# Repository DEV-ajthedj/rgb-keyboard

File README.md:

My first hack club project!

This repository holds my first hack club project, which is building a keyboard complete with an ergonomic design and a cool display.

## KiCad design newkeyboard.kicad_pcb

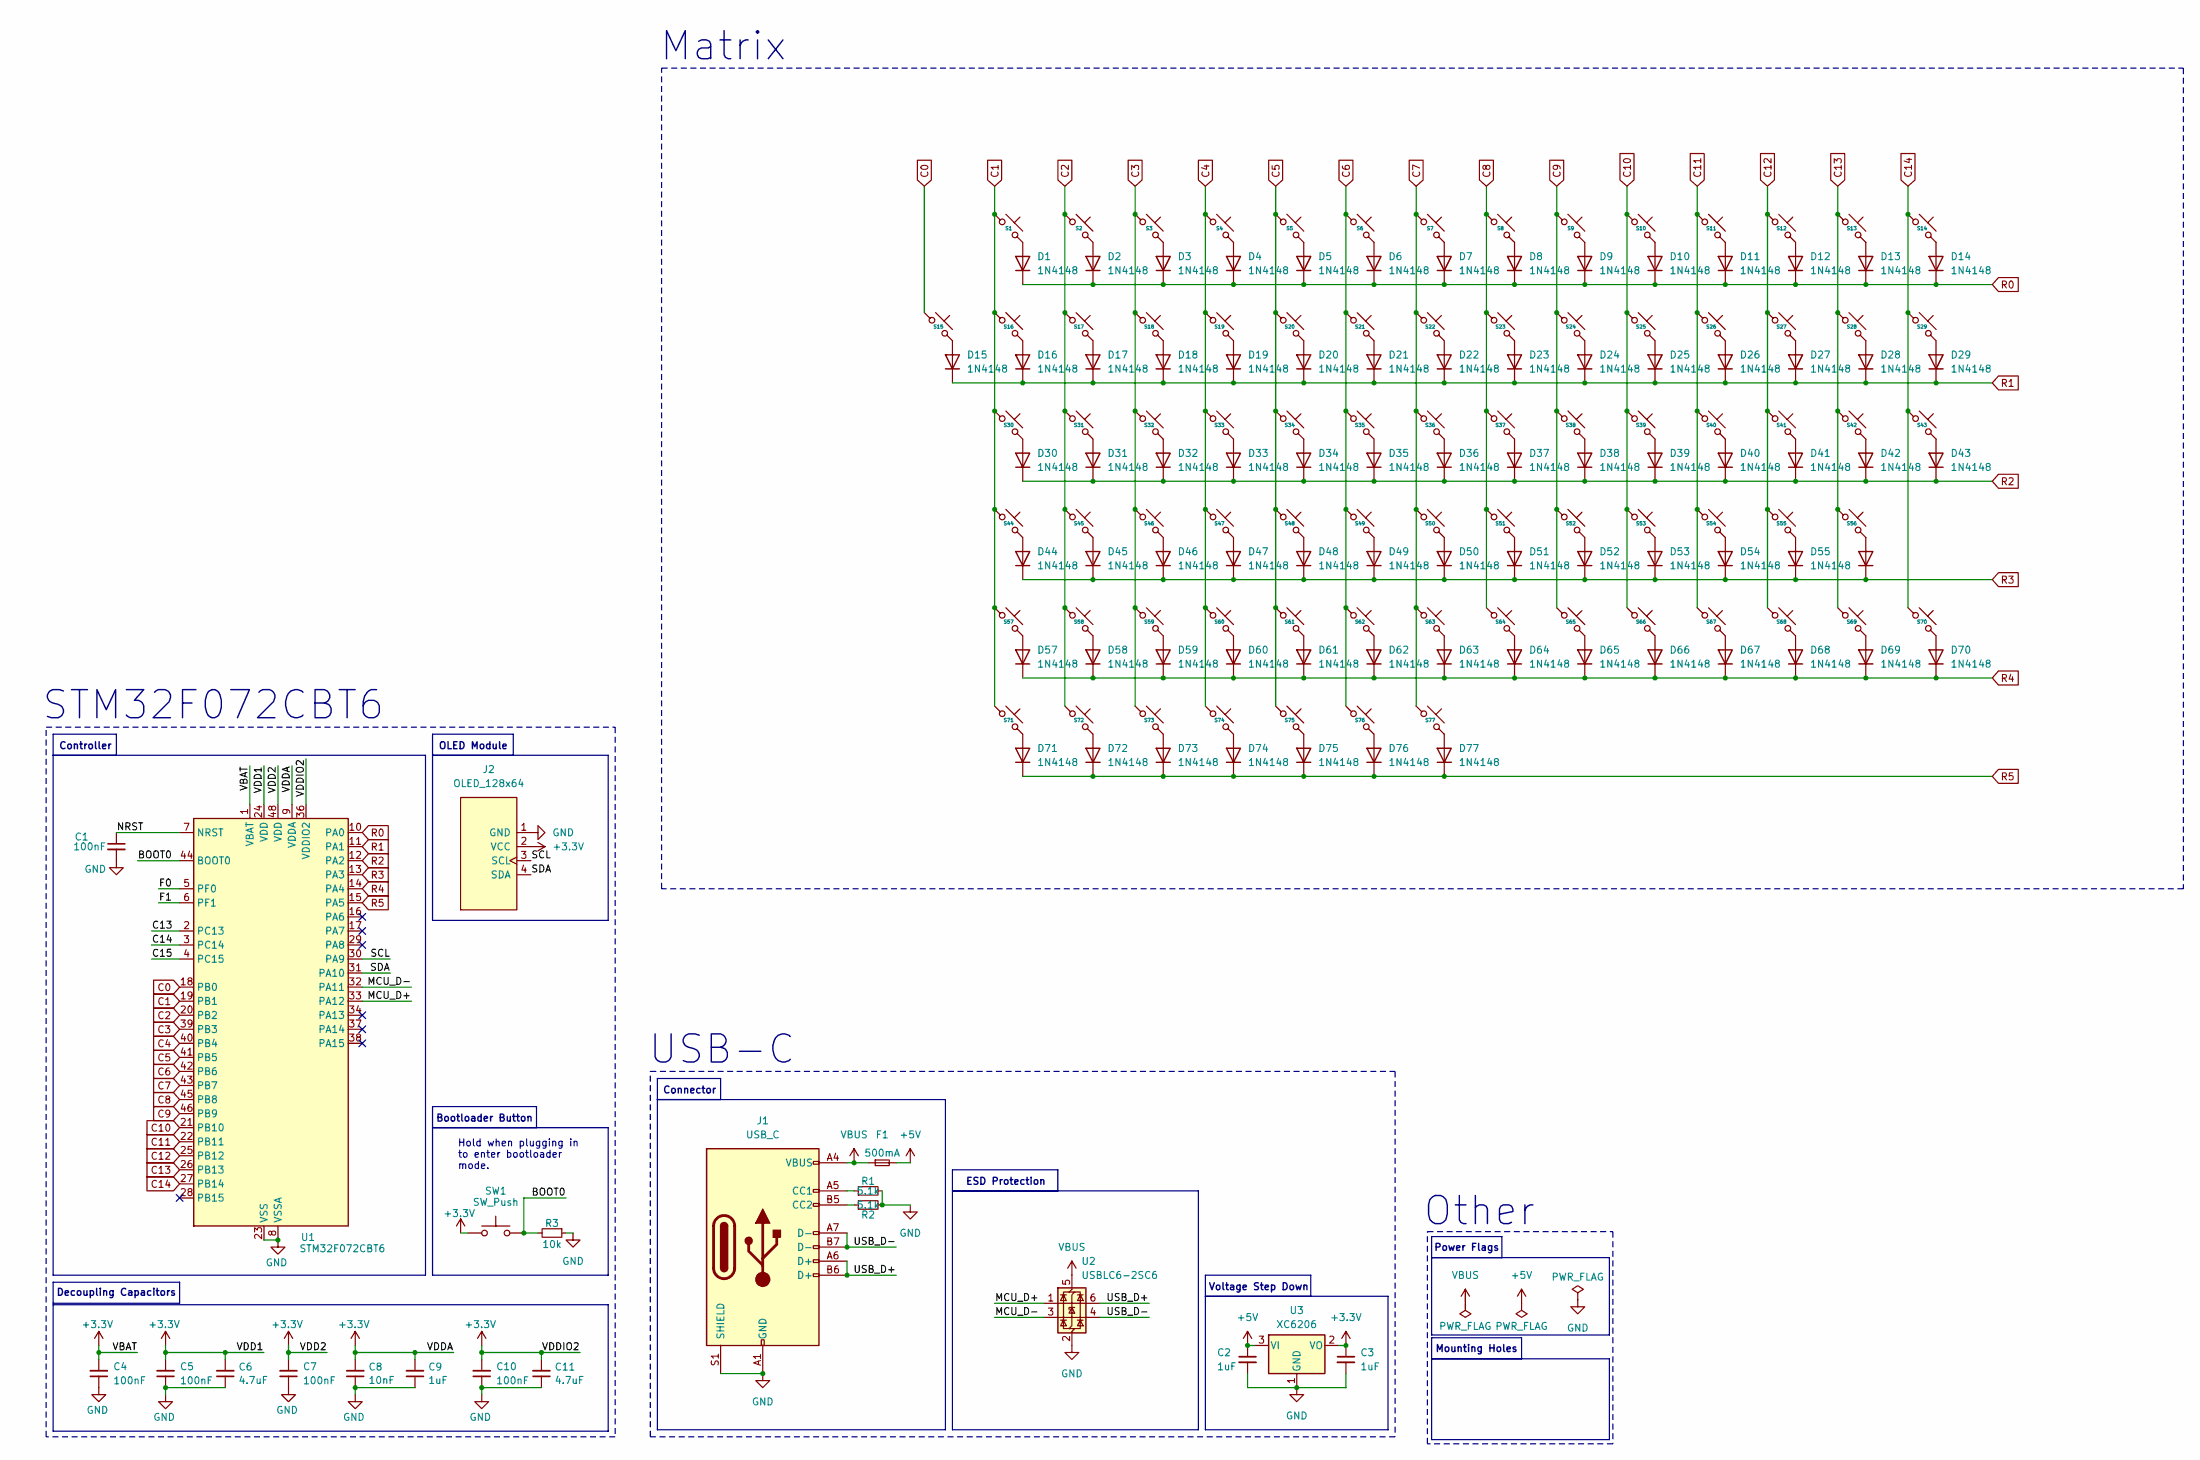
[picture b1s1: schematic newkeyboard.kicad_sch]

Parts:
C1: 100nF; Capacitor_0402; LCSC C307331
C2, C3: 1uF; Capacitor_0402; LCSC C52923
C4, C5, C7, C10: 100nF; Capacitor_0402; MPN CL05B104KB54PNC; LCSC C307331
C6, C11: 4.7uF; Capacitor_0402; MPN CL05A475MP5NRNC; LCSC C23733
C8: 10nF; Capacitor_0402; MPN CL05B103KB5NNNC; LCSC C15195
C9: 1uF; Capacitor_0402; MPN CL05A105KA5NQNC; LCSC C52923
D1, D2, D3, D4, D5, D6, D7, D8, D9, D10, D11, D12, D13, D14, D15, D16, D17, D18, D19, D20, D21, D22, D23, D24, D25, D26, D27, D28, D29, D30, D31, D32, D33, D34, D35, D36, D37, D38, D39, D40, D41, D42, D43, D44, D45, D46, D47, D48, D49, D50, D51, D52, D53, D54, D55, D56, D57, D58, D59, D60, D61, D62, D63, D64, D65, D66, D67, D68, D69, D70, D71, D72, D73, D74, D75, D76, D77: 1N4148; Diode_SOD-123
F1: 500mA; Fuse_0603; LCSC C210357
J1: USB_C; USB_C_HRO_TYPE-C-31-M-12; LCSC C165948
J2: OLED_128x64
R1, R2: 5.1k; Resistor_0402; LCSC C25905
R3: 10k; Resistor_0402; LCSC C25744
S1, S2, S3, S4, S5, S6, S7, S8, S9, S10, S11, S12, S13, S14, S15, S16, S17, S18, S19, S20, S21, S22, S23, S24, S25, S26, S27, S28, S29, S30, S31, S32, S33, S34, S35, S36, S37, S38, S39, S40, S41, S42, S43, S44, S45, S46, S47, S48, S49, S50, S51, S52, S53, S54, S55, S56, S57, S58, S59, S60, S61, S62, S63, S64, S65, S66, S67, S68, S69, S70, S71, S72, S73, S74, S75, S76, S77: SW_SPST; Hotswap_MX
SW1: SW_Push; Button_TL3342; LCSC C115351
U1: STM32F072CBT6; Package_LQFP-48_7x7mm_P0.5; LCSC C81720
U2: USBLC6-2SC6; ESD_SOT-23-6; LCSC C2827654
U3: XC6206; Voltage_SOT-23; LCSC C5446

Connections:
+3.3V: C3.1, C4.2, C5.2, C6.2, C7.2, C8.2, C9.2, C10.2, C11.2, J2.2 (VCC), SW1.1, U1.1 (VBAT), U1.9 (VDDA), U1.24 (VDD), U1.36 (VDDIO2), U1.48 (VDD), U3.2 (VO)
+5V: C2.1, F1.2, U3.3 (VI)
/BOOT0: R3.2, SW1.2, U1.44 (BOOT0)
/C15: U1.4 (PC15)
/F0: U1.5 (PF0)
/F1: U1.6 (PF1)
/MCU_D+: U1.33 (PA12), U2.1 (I/O1)
/MCU_D-: U1.32 (PA11), U2.3 (I/O2)
/NRST: C1.1, U1.7 (NRST)
/SCL: J2.3 (SCL), U1.30 (PA9)
/SDA: J2.4 (SDA), U1.31 (PA10)
/USB_D+: J1.A6 (D+), J1.B6 (D+), U2.6 (I/O1)
/USB_D-: J1.A7 (D-), J1.B7 (D-), U2.4 (I/O2)
C0: S15.1, U1.18 (PB0)
C1: S1.1, S16.1, S30.1, S44.1, S57.1, S71.1, U1.19 (PB1)
C2: S2.1, S17.1, S31.1, S45.1, S58.1, S72.1, U1.20 (PB2)
C3: S3.1, S18.1, S32.1, S46.1, S59.1, S73.1, U1.39 (PB3)
C4: S4.1, S19.1, S33.1, S47.1, S60.1, S74.1, U1.40 (PB4)
C5: S5.1, S20.1, S34.1, S48.1, S61.1, S75.1, U1.41 (PB5)
C6: S6.1, S21.1, S35.1, S49.1, S62.1, S76.1, U1.42 (PB6)
C7: S7.1, S22.1, S36.1, S50.1, S63.1, S77.1, U1.43 (PB7)
C8: S8.1, S23.1, S37.1, S51.1, S64.1, U1.45 (PB8)
C9: S9.1, S24.1, S38.1, S52.1, S65.1, U1.46 (PB9)
C10: S10.1, S25.1, S39.1, S53.1, S66.1, U1.21 (PB10)
C11: S11.1, S26.1, S40.1, S54.1, S67.1, U1.22 (PB11)
C12: S12.1, S27.1, S41.1, S55.1, S68.1, U1.25 (PB12)
C13: S13.1, S28.1, S42.1, S56.1, S69.1, U1.2 (PC13), U1.26 (PB13)
C14: S14.1, S29.1, S43.1, S70.1, U1.3 (PC14), U1.27 (PB14)
GND: C1.2, C2.2, C3.2, C4.1, C5.1, C6.1, C7.1, C8.1, C9.1, C10.1, C11.1, J1.A1 (GND), J1.A12 (GND), J1.B1 (GND), J1.B12 (GND), J1.S1 (SHIELD), J2.1 (GND), R1.2, R2.2, R3.1, U1.8 (VSSA), U1.23 (VSS), U1.35 (VSS), U1.47 (VSS), U2.2 (GND), U3.1 (GND)
unnamed: D1.2 (A), S1.2
unnamed: D2.2 (A), S2.2
unnamed: D3.2 (A), S3.2
unnamed: D4.2 (A), S4.2
unnamed: D5.2 (A), S5.2
unnamed: D6.2 (A), S6.2
unnamed: D7.2 (A), S7.2
unnamed: D8.2 (A), S8.2
unnamed: D9.2 (A), S9.2
unnamed: D10.2 (A), S10.2
unnamed: D11.2 (A), S11.2
unnamed: D12.2 (A), S12.2
unnamed: D13.2 (A), S13.2
unnamed: D14.2 (A), S14.2
unnamed: D15.2 (A), S15.2
unnamed: D16.2 (A), S16.2
unnamed: D17.2 (A), S17.2
unnamed: D18.2 (A), S18.2
unnamed: D19.2 (A), S19.2
unnamed: D20.2 (A), S20.2
unnamed: D21.2 (A), S21.2
unnamed: D22.2 (A), S22.2
unnamed: D23.2 (A), S23.2
unnamed: D24.2 (A), S24.2
unnamed: D25.2 (A), S25.2
unnamed: D26.2 (A), S26.2
unnamed: D27.2 (A), S27.2
unnamed: D28.2 (A), S28.2
unnamed: D29.2 (A), S29.2
unnamed: D30.2 (A), S30.2
unnamed: D31.2 (A), S31.2
unnamed: D32.2 (A), S32.2
unnamed: D33.2 (A), S33.2
unnamed: D34.2 (A), S34.2
unnamed: D35.2 (A), S35.2
unnamed: D36.2 (A), S36.2
unnamed: D37.2 (A), S37.2
unnamed: D38.2 (A), S38.2
unnamed: D39.2 (A), S39.2
unnamed: D40.2 (A), S40.2
unnamed: D41.2 (A), S41.2
unnamed: D42.2 (A), S42.2
unnamed: D43.2 (A), S43.2
unnamed: D44.2 (A), S44.2
unnamed: D45.2 (A), S45.2
unnamed: D46.2 (A), S46.2
unnamed: D47.2 (A), S47.2
unnamed: D48.2 (A), S48.2
unnamed: D49.2 (A), S49.2
unnamed: D50.2 (A), S50.2
unnamed: D51.2 (A), S51.2
unnamed: D52.2 (A), S52.2
unnamed: D53.2 (A), S53.2
unnamed: D54.2 (A), S54.2
unnamed: D55.2 (A), S55.2
unnamed: D56.2 (A), S56.2
unnamed: D57.2 (A), S57.2
unnamed: D58.2 (A), S58.2
unnamed: D59.2 (A), S59.2
unnamed: D60.2 (A), S60.2
unnamed: D61.2 (A), S61.2
unnamed: D62.2 (A), S62.2
unnamed: D63.2 (A), S63.2
unnamed: D64.2 (A), S64.2
unnamed: D65.2 (A), S65.2
unnamed: D66.2 (A), S66.2
unnamed: D67.2 (A), S67.2
unnamed: D68.2 (A), S68.2
unnamed: D69.2 (A), S69.2
unnamed: D70.2 (A), S70.2
unnamed: D71.2 (A), S71.2
unnamed: D72.2 (A), S72.2
unnamed: D73.2 (A), S73.2
unnamed: D74.2 (A), S74.2
unnamed: D75.2 (A), S75.2
unnamed: D76.2 (A), S76.2
unnamed: D77.2 (A), S77.2
unnamed: J1.A5 (CC1), R1.1
unnamed: J1.B5 (CC2), R2.1
R0: D1.1 (K), D2.1 (K), D3.1 (K), D4.1 (K), D5.1 (K), D6.1 (K), D7.1 (K), D8.1 (K), D9.1 (K), D10.1 (K), D11.1 (K), D12.1 (K), D13.1 (K), D14.1 (K), U1.10 (PA0)
R1: D15.1 (K), D16.1 (K), D17.1 (K), D18.1 (K), D19.1 (K), D20.1 (K), D21.1 (K), D22.1 (K), D23.1 (K), D24.1 (K), D25.1 (K), D26.1 (K), D27.1 (K), D28.1 (K), D29.1 (K), U1.11 (PA1)
R2: D30.1 (K), D31.1 (K), D32.1 (K), D33.1 (K), D34.1 (K), D35.1 (K), D36.1 (K), D37.1 (K), D38.1 (K), D39.1 (K), D40.1 (K), D41.1 (K), D42.1 (K), D43.1 (K), U1.12 (PA2)
R3: D44.1 (K), D45.1 (K), D46.1 (K), D47.1 (K), D48.1 (K), D49.1 (K), D50.1 (K), D51.1 (K), D52.1 (K), D53.1 (K), D54.1 (K), D55.1 (K), D56.1 (K), U1.13 (PA3)
R4: D57.1 (K), D58.1 (K), D59.1 (K), D60.1 (K), D61.1 (K), D62.1 (K), D63.1 (K), D64.1 (K), D65.1 (K), D66.1 (K), D67.1 (K), D68.1 (K), D69.1 (K), D70.1 (K), U1.14 (PA4)
R5: D71.1 (K), D72.1 (K), D73.1 (K), D74.1 (K), D75.1 (K), D76.1 (K), D77.1 (K), U1.15 (PA5)
VBUS: F1.1, J1.A4 (VBUS), J1.A9 (VBUS), J1.B4 (VBUS), J1.B9 (VBUS), U2.5 (VBUS)

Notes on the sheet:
STM32F072CBT6
USB-C
Mounting Holes
OLED Module
Decoupling Capacitors
Controller
ESD Protection
Power Flags
Voltage Step Down
Other
Bootloader Button
Matrix
Connector
Hold when plugging in to enter bootloader mode.

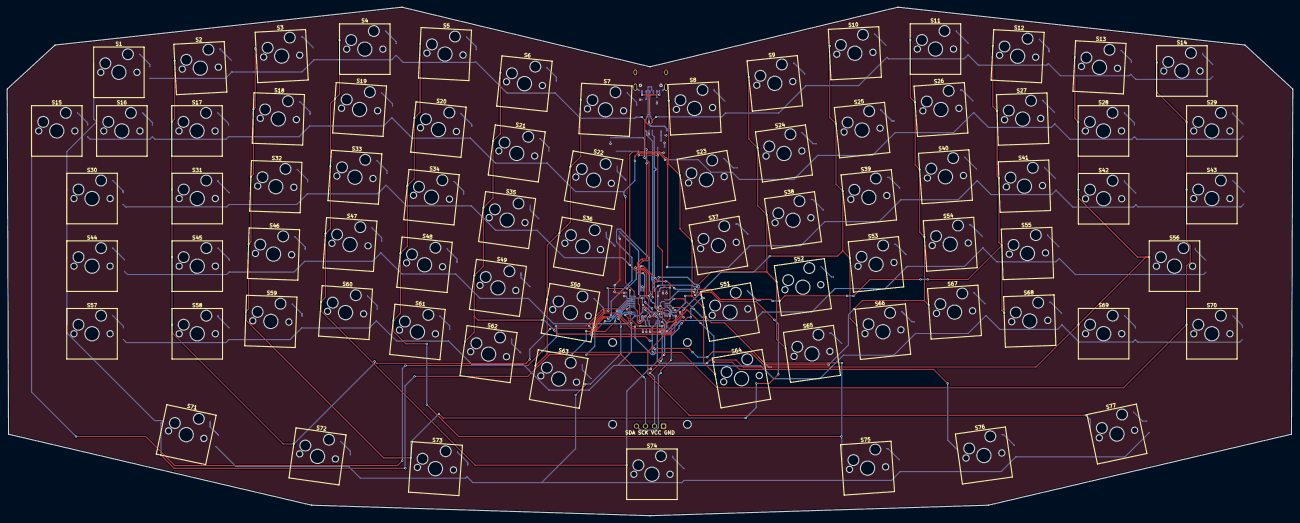
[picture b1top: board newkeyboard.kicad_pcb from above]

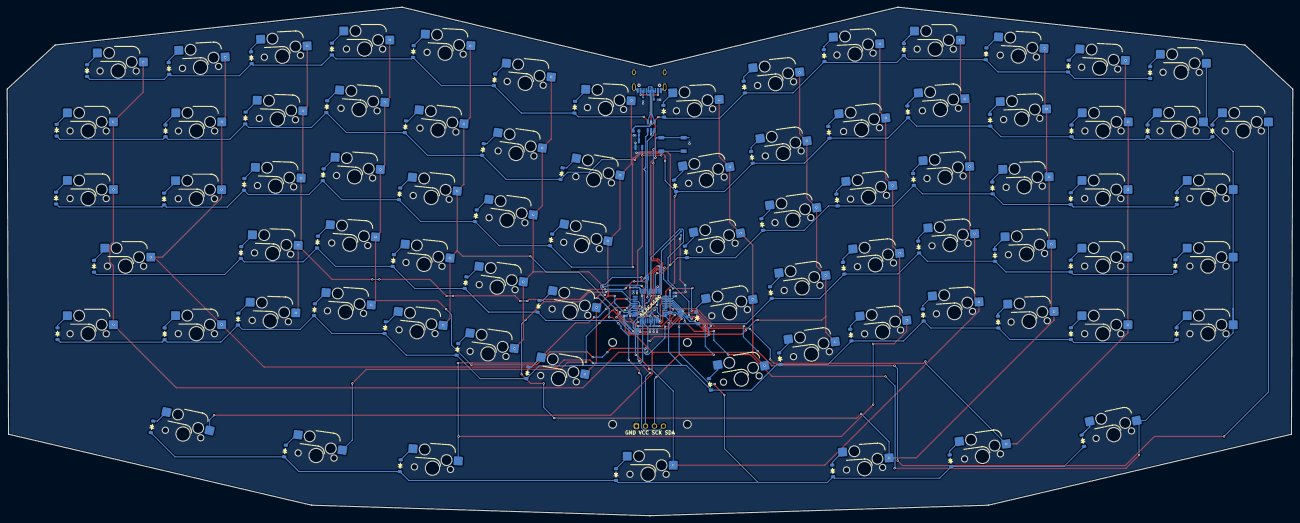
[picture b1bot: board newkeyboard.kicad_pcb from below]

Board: 2 copper layers, 361.3 x 142.9 mm, 175 parts (97 on the bottom side), 112 nets.

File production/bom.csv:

Designator,Footprint,Quantity,Value,LCSC Part #
"C1, C10, C4, C5, C7",Capacitor_0402,5,100nF,
"C11, C6",Capacitor_0402,2,4.7uF,
"C2, C3, C9",Capacitor_0402,3,1uF,
C8,Capacitor_0402,1,10nF,
"D1, D10, D11, D12, D13, D14, D15, D16, D17, D18, D19, D2, D20, D21, D22, D23, D24, D25, D26, D27, D28, D29, D3, D30, D31, D32, D33, D34, D35, D36, D37, D38, D39, D4, D40, D41, D42, D43, D44, D45, D46, D47, D48, D49, D5, D50, D51, D52, D53, D54, D55, D56, D57, D58, D59, D6, D60, D61, D62, D63, D64, D65, D66, D67, D68, D69, D7, D70, D71, D72, D73, D74, D75, D76, D77, D8, D9",Diode_SOD-123,77,1N4148,
F1,Fuse_0603,1,500mA,
J1,USB_C_HRO_TYPE-C-31-M-12,1,USB_C,
J2,OLED_128x64,1,OLED_128x64,
"R1, R2",Resistor_0402,2,5.1k,
R3,Resistor_0402,1,10k,
"S1, S10, S11, S12, S13, S14, S15, S16, S17, S18, S19, S2, S20, S21, S22, S23, S24, S25, S26, S27, S28, S29, S3, S30, S31, S32, S33, S34, S35, S36, S37, S38, S39, S4, S40, S41, S42, S43, S44, S45, S46, S47, S48, S49, S5, S50, S51, S52, S53, S54, S55, S56, S57, S58, S59, S6, S60, S61, S62, S63, S64, S65, S66, S67, S68, S69, S7, S70, S71, S72, S73, S74, S75, S76, S77, S8, S9",Hotswap_MX,77,SW_SPST,
SW1,Button_TL3342,1,SW_Push,
U1,Package_LQFP-48_7x7mm_P0.5,1,STM32F072CBT6,
U2,ESD_SOT-23-6,1,USBLC6-2SC6,
U3,Voltage_SOT-23,1,XC6206,

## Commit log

2026-04-08 Actual Initial Commit
2026-04-08 Completed virtually all of keyboard design
2026-04-22 Revise project description in README
    Updated project description to mention a cool display.
2026-04-22 KICAD design
